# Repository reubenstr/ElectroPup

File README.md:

# ElectroPup

ElectroPup is a DIY 3D-printed quadruped robot using 'low cost' BLDC motors.

[Video of kinematic poses](https://youtu.be/AJn_wCcWlwo)

[Video of walking, turning, strafing](https://youtu.be/YjTVNw8BXlM)

## Basic Specifications

- RPi 5
- 12x BLDC motors
- Auxiliary board w/LCD display
- 9-axis accelerometer/gyro sensor
- 6s Li-Ion battery, ~72wH
- 4.5kg

ElectroPup's control system is coded in Python. For a ROS2 based quadruped, see my previous project [Zuko](https://github.com/reubenstr/zuko).

# Docs

See the docs directory for a setup guide, bill of materials (BOM), 3D printed parts info, and miscellaneous design notes.

# UI

The UI shows the status of the entire system: quadruped joint positions, subsystem status, motor information, inputs, sensors, loop times, etc. The above image shows the simulated quadruped overlapped with real quadruped (based on motor feedback).

The above image shows a virtual circle the feet follow to walk in a circle and the bezier curves used for moving the feet up and down.

The UI is built from the React Native Framework using Expo and runs on web. The app will run on Android without the plot. The entire system runs in dev mode so you can run the simulation and UI from a development PC without physical hardware.

# Kinematics

Inverse kinematics, leg position, and gamepad inputs are verified using the UI.

### Trajectories

Bezier curves, sin arcs, and curvature projection are used to generate trajectories. The plots below are examples of control points configurations. 

The output of `./src/plot/bezier_curve_plot.py`

Rotation is achieved by projecting a linear trajectory onto a curve. The plots are of example projection calculations.

The output of `./src/plot/projection_plot.py`

# Simulation

Simulation is performed in [MuJoCo](https://mujoco.org/) and can be started by running `./src/sim.sh`. Currently, input controlls are only provided by the gamepad. The `ElectroPup.xml` currently does not have approximate masses or inertial so the simulated quadruped is rather bouncy.

# Electronics

## PCBs

PCBs are designed in [KiCad](https://www.kicad.org/) v8 and fabricated by JLCPCB.

### Power Carrier

The Power Carrier PCB provides a main on/off power switch and distributes power to the motor headers. The Power Carrier creates four CAN bus networks one for each leg. Solder jumpers allow merging the front two legs into a single network and the back two legs into another single network.

### Auxiliary Board

The auxiliary board is optional and not required for the quadruped to operate.

Features:
- Powers RPi via terminal header
- LCD display
- Buzzer (variable pitch)
- NeoPixel strips
- RC Servo channel
- I2C expansion
- Button to control LCD and shutdown Raspberry Pi before power off

Provides direct connection to RPi header for the following breakouts:
- IMU (BNO055 via I2C)
- 4x contact inputs or GPIO
- I2S for sound driver (future barks 🐶)
- SBUS to use RC transmitter if BLE gamepad fails in RF congested areas

# Software Architecture

Electropup's software architecture was purposely designed to be simple and to bypass the pain points of using ROS2. See my [Zuko]( https://github.com/reubenstr/zuko) robot quadruped for a ROS2 implementation, abiet outdated. A major downside of this single service architecture is needing to sit and stand the quadruped on every software change vs being able to restart individual services quickly without affecting others (i.e. the motors). However, with the simulated quadruped and UI, most development is not performed on a live quadruped.

# Motors

The motors are MG4010E-i10v3 actuators made by LingKong (LKMTECH) and can be purchased from [Aliexpress](https://www.aliexpress.us/item/3256805950420462.html?spm=a2g0o.order_list.order_list_main.5.32491802no3XMa&gatewayAdapt=glo2usa).

### Specifications
- voltage: 7.4-32V
- communication: CAN 1Mbps
- rated torque: 2.5 N.m
- max torque: 4.5 N.m
- rated current: 3.5 A
- max power: 140 W
- gear ratio: 1:10
- encoders: 18-bit motor, 14-bit reducer
- size: 53mm diameter, 41mm tall
- weight: 238 grams

### MG4010E-i10v3 Pros
- easy to use configuration software over non-proprietary USB to UART hardware
- readable CAN bus communication documentation
- small physical size that works well with the desired frame size of ElectroPup
- non-proprietary power/communications connector (JST-ZH 6-POS)

### MG4010E-i10v3 Cons
- configuration software is Windows only
- closed source firmware
- foreign sourced, complicating the warranty process
- CAN unable to configure all parameters
- UART required to configure error thresholds, motor torque limits (for compliance), etc.
- some motors are more difficult to turn by hand and require slightly more operational current

Future projects will prioritize ODrive compatible drivers.

### Motor Zero Positions

### Motor Tags

### Motor Calibration

The zero-motors.py script is a quick way to verify correct motor configuration and to zero the motors.

# CAN Bus

The CAN bus controller is a [2-Channel Isolated CAN Expansion HAT](https://www.waveshare.com/2-ch-can-hat.htm) from waveshare.

Each CAN controller drives six motors with an average motor update rate of ~70 Hz. This includes fetching encoder position, setting target angle/speed, and getting error states.

# Gamepad

ElectroPup was coded with a PS4 controller in mind, however xBox, PS5, Logitech gamepads may be used with minor software modifications.

# Environment and IDEs 

There are three hardware/software environments described below.

### PC/Laptop - Plotting, Simulation, and Development

Desktop or laptop computer running Ubuntu Desktop (or your preferred flavor of Linux).

Software: VSCode (with remote SSH and PlatformIO extensions), Drawio, LibreOffice, KiCad, OrcaSlicer, Chrome/Firefox

### Raspberry Pi - Quadruped Hardware Driver

The quadruped compute is a Raspberry Pi 5.

The OS is Raspberry Pi OS Lite (Bookworm 64-bit), which is headless, so all development is performed using remote SSH.

### STM32 - Auxiliary Board

An STM32F401 Black Pill dev kit operates the auxiliary board to display the motor and system status on a LCD display and interface with other peripherals such as the buzzer. 

Uses VSCode with PlatformIO on the PC/Laptop for development.

# Parts

The 3D printed parts are printed using Polymaker PolyMax Tough PLA selected for strength and ease of printing. See these excellent blog posts for more information: [cnckitchen](https://www.cnckitchen.com/blog/the-difference-of-pla-and-pla-tested-feat-polymaker) and [edemargerie](https://www.instructables.com/Comparing-Impact-Resistance-of-21-Filaments-for-3D/).

| Color          | Estimated Print Time | Estimated Filament |
| -------------- | -------------------- | ------------------ |
| main (red)     | 25.23 hours          | 742 grams          |
| accent (black) | 3.58 hours           | 92 grams           |

### CAD

Parts are modeled using [OnShape](https://www.onshape.com/en/) which provides free web-based full access for non-commercial use. The links below should have export permissions to allow copying the workspace.

- [Assembly](https://cad.onshape.com/documents/b02341d4ebb7f3e9dd488186)
- [Legs](https://cad.onshape.com/documents/6da583196278caf8e90b3122)
- [Body](https://cad.onshape.com/documents/280c24f1b6bdbe8246159786)
- [Hips](https://cad.onshape.com/documents/428031d0c98bf15dcc9f5c8c)
- [Tools](https://cad.onshape.com/documents/3677b35bffbfedb5a3fd2b26)
- [Parts](https://cad.onshape.com/documents/6d4d4e21394ee725ee8ddb38)
- [PCB](https://cad.onshape.com/documents/c8a855826c37bd92b89d9f0e)
- [Neopixels](https://cad.onshape.com/documents/567292ac55c75b2efa25b7d5)

# Battery Pack 

The battery is a custom 6S1P Li-Ion using 18650s with a load balancing BMS. The 18650's are Sanyo branded and rated at 3250mAH each providing an estimated 72Wh.

The above image is showing work in progress. The [insulation rings](https://imrbatteries.com/products/18650-terminal-insulators-fish-paper-20pcs-green-round-rings) were forgotten during fabrication and really should be mandatory for any battery build. 

The BMS is a HXYP-6S-CW15.

# Future Improvements  

This is a general improvement list for future updates or revisions. 

- add upside down control (the frame supports walking even after flipped)
- apply IMU for smoother gaits
- add center of mass calculations for smoother gaits
- swap battery and RPi positions for better center of mass
- swap foot lag bolt from SAE to metric
- add curvature to lower leg
- add speaker for barks
- add a tail
- add voltage/current sensor (such as an INA228)
- remove STM32 from aux board and use RPI directly for buzzer, LCD, etc.
- create a [MPC](https://en.wikipedia.org/wiki/Model_predictive_control) controller

# Thoughts

- Due to a lower power consumption than estimated, a larger frame and longer legs can be created. A larger frame would support moving the knee motor to the hip area allowing the lower leg to be belt driven. The reduction of mass of the knee will increase center of mass stability and create smoother gaits.
- Future Auxiliary board revisions will remove the STM32 and either drive the LCD directly from the RPi or remove it completely. The extra complexity outweighs the LCD's usefulness, especially when the GUI provides significantly more data.
- Future power carrier PCB revisions will include a voltage/current sensor such as a INA228 and a fuse.
- The carbon rods twist during the run gait which can be reduced by extending the rods through the hip plates and adding face / butt plates. 
- Future revisions will prioritize adding contact sensors that will allow for better terrain handling and future AI training.
- A full architecture refactor splitting major components into services would have the advantages of individual unit testing and keeping the quadruped standing during development.

# Questions

For any questions please post a new [issue](https://github.com/reubenstr/ElectroPup/issues) on the repo's GitHub page.

# Credits

Inverse kinematics and leg points for plotting were sourced from mike4192: [https://github.com/mike4192/](https://github.com/mike4192/).

Using carbon fiber tube as frame supports inspired from [Open Dog 3](https://www.youtube.com/watch?v=ts2l_Em7fpI&list=PLpwJoq86vov8uTgd8_WNgBHFpDYemO-OJ&index=3) by James Bruton.

There are many excellent open source quadruped robot projects at various sizes, costs, and complexity. Below are projects and code examples worth checking out.

- https://github.com/mit-biomimetics/Cheetah-Software
- https://github.com/mike4192/spotMicro
- https://github.com/mike4192/spot_micro_kinematics_python
- https://spotmicroai.readthedocs.io/en/latest/
- https://github.com/adham-elarabawy/open-quadruped
- https://www.youtube.com/jamesbruton
- https://github.com/chvmp/champ
- https://grabcad.com/library/diy-quadruped-robot-1
- https://github.com/Jerome-Graves/yertle
- https://www.youtube.com/@Jorgefer88
- https://www.youtube.com/watch?v=oYnsCE2H6ss
- https://github.com/JackDemeter/quadruped-robot
- https://github.com/reubenstr/zuko

# AI Disclosure

Project concept, aesthetic, engineering design, and original code base were conceived and executed by the author.

Portions of this codebase were reviewed, revised, and written with the assistance of Claude Code (Anthropic).

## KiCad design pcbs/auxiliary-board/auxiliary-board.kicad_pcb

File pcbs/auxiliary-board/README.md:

# TODO / Fixes

- Add version number to silkscreen
- Change terminal footprint to match the now used terminal: WM7877-ND 
- Add a switch for WiFi AP/Client switching
- LCD holes are not aligned and are off slightly
- Change 40 pin header from SMD to through-hold
- Consider adding a second tactile button

# General Thoughts

- Removing the Black Pill in favor of using a STM32 directly on the board will save space and allow the addition of more breakouts such as buttons.

- Removing the LCD PCB and directly connecting a LCD to the board will reduce the height of the board that will decrease the chance of screen damage when the quadruped rolls over.

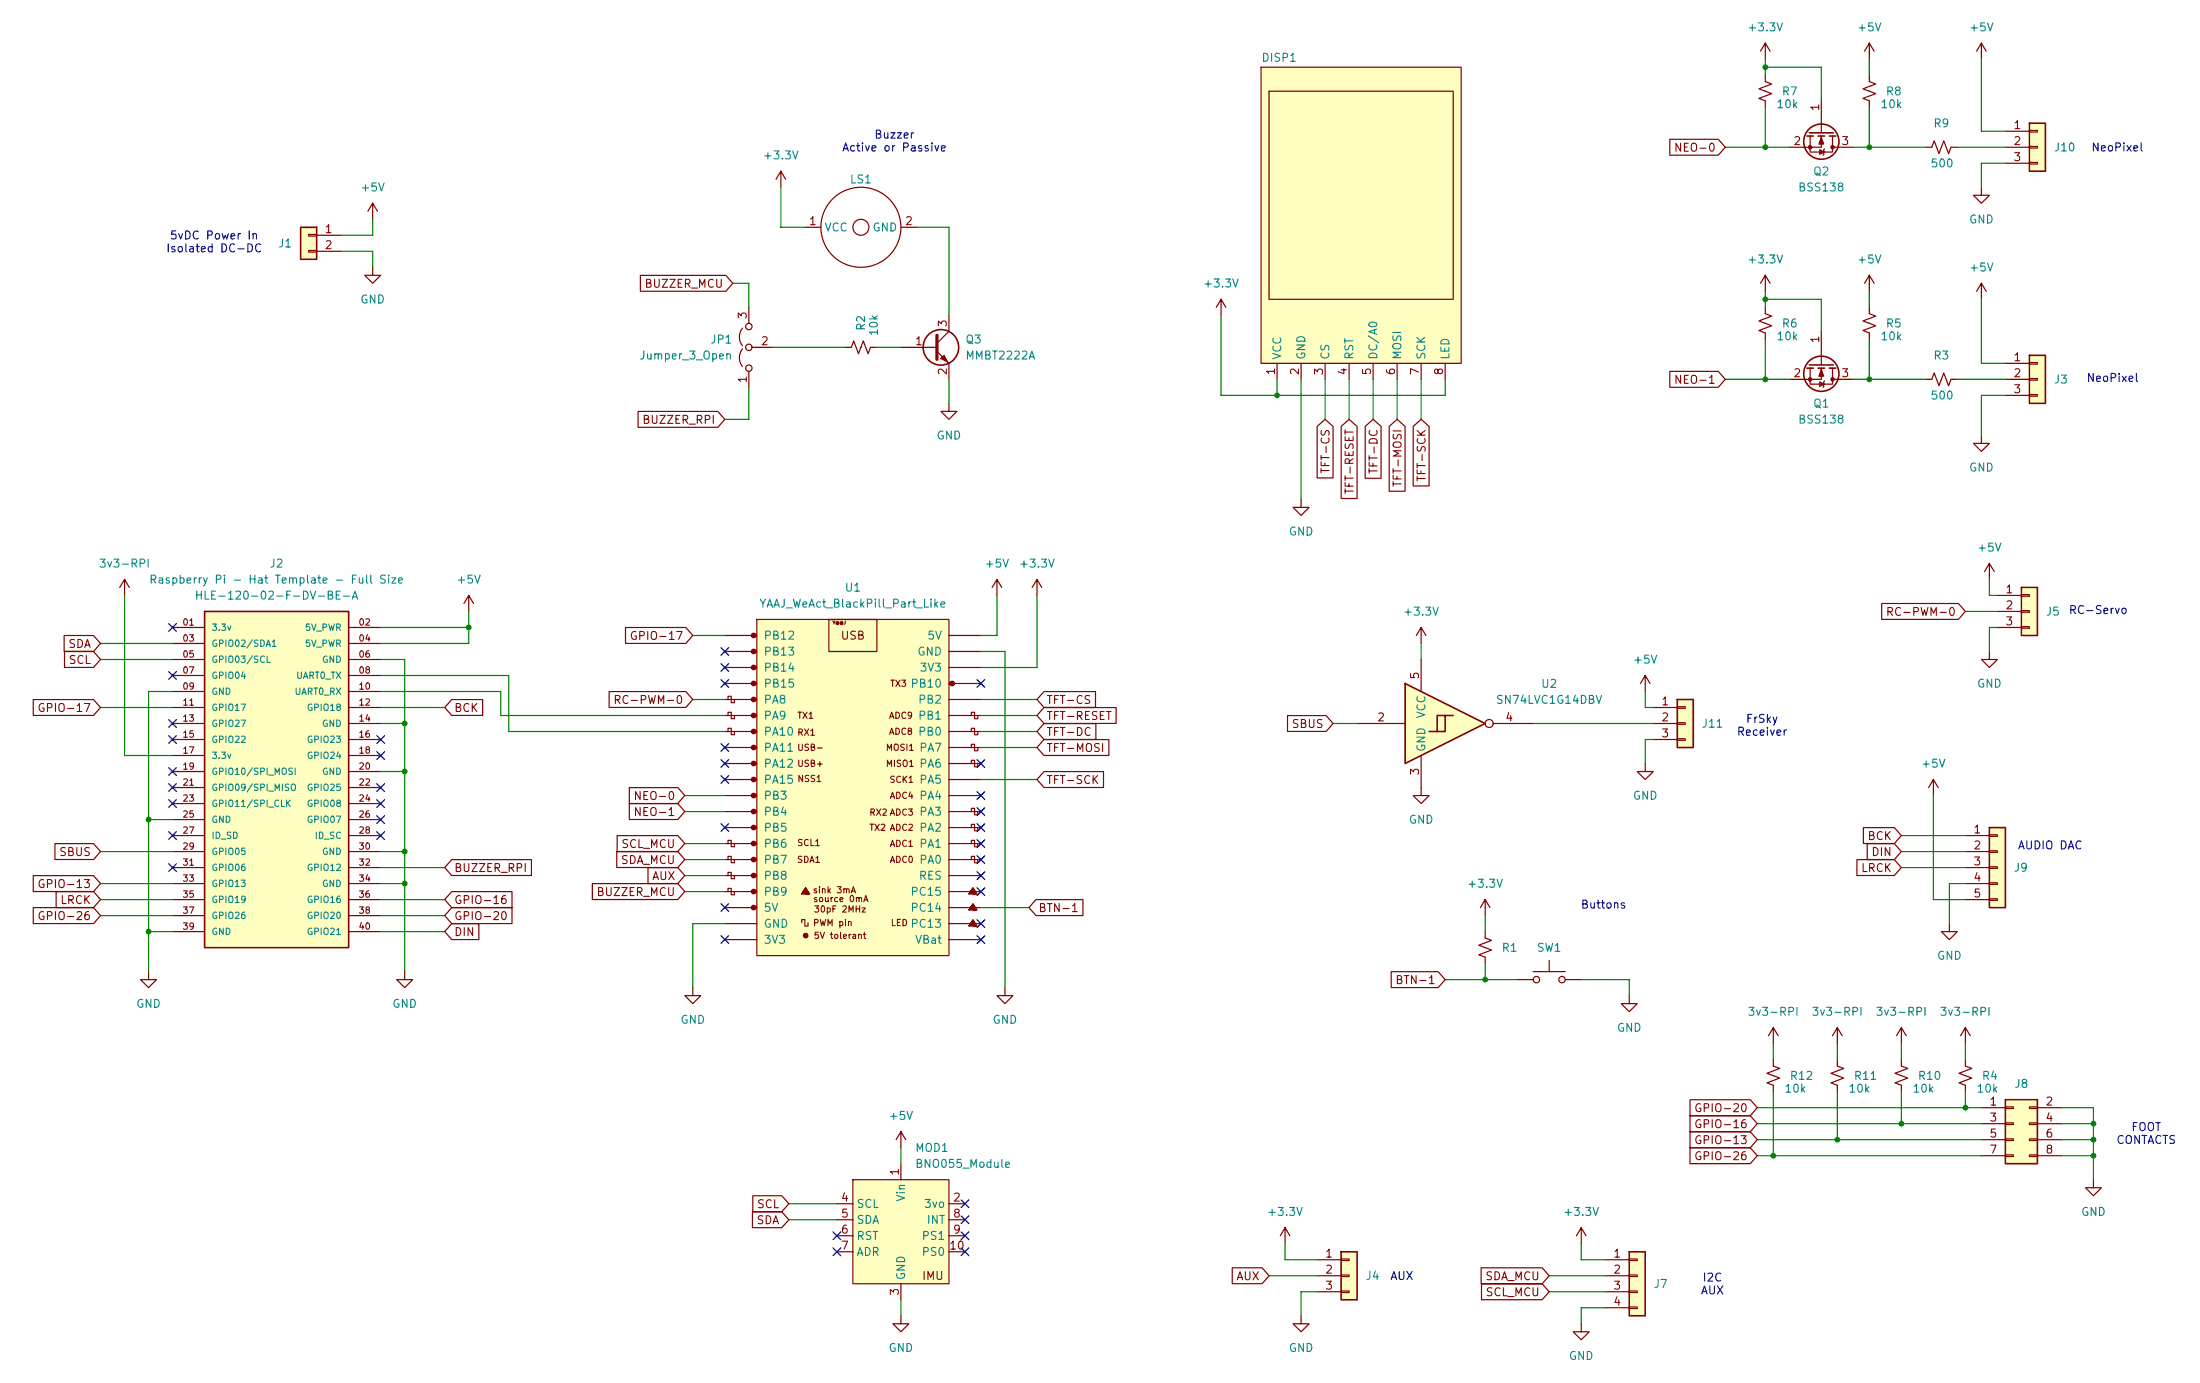
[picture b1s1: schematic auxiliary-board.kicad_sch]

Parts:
DISP1: LCD-Display-1.8-128x160-Hiletgo
J1: Conn_01x02; TerminalBlock_Phoenix_PT-1,5-2-3.5-H_1x02_P3.50mm_Horizontal
J2: Raspberry Pi - Hat Template - Full Size; Raspberry Pi - Hat Template - Full Size Extended
J3, J4, J5, J10, J11: Conn_01x03; JST_ZH_B3B-ZR_1x03_P1.50mm_Vertical
J7: Conn_01x04; JST_ZH_B4B-ZR_1x04_P1.50mm_Vertical
J8: Conn_02x04_Odd_Even; PinHeader_2x04_P2.54mm_Vertical
J9: Conn_01x05; JST_ZH_B5B-ZR_1x05_P1.50mm_Vertical
JP1: Jumper_3_Open; SolderJumper-3_P1.3mm_Open_Pad1.0x1.5mm
LS1: PB-09N23P-03Q_MAL
MOD1: BNO055_Module; BNO055 Module
Q1, Q2: BSS138; SOT-23
Q3: MMBT2222A; SOT-23
R1: R_Small_US; R_1206_3216Metric
R2, R4, R5, R6, R7, R8, R10, R11, R12: 10k; R_1206_3216Metric
R3, R9: 500; R_1206_3216Metric
SW1: SW_Push; SW_PUSH_6mm_H4.3mm
U1: YAAJ_WeAct_BlackPill_Part_Like; Blackpill WeAct
U2: SN74LVC1G14DBV; SOT-23-5

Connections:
3v3-RPI: J2.17 (3.3v), R4.2, R10.2, R11.2, R12.2
+3.3V: DISP1.1 (VCC), DISP1.8 (LED), J4.1, J7.1, LS1.1 (VCC), Q1.1 (G), Q2.1 (G), R1.2, R6.2, R7.2, U1.38 (3V3), U2.5 (VCC)
+5V: J1.1, J2.02 (5V_PWR), J2.04 (5V_PWR), J3.1, J5.1, J9.5, J10.1, J11.1, MOD1.1 (Vin), R5.2, R8.2, U1.40 (5V)
AUX: J4.2, U1.16 (PB8)
BCK: J2.12 (GPIO18), J9.1
BTN-1: R1.1, SW1.1, U1.23 (PC14)
BUZZER_MCU: JP1.3 (B), U1.17 (PB9)
BUZZER_RPI: J2.32 (GPIO12), JP1.1 (A)
DIN: J2.40 (GPIO21), J9.2
GND: DISP1.2 (GND), J1.2, J2.06 (GND), J2.09 (GND), J2.14 (GND), J2.20 (GND), J2.25 (GND), J2.30 (GND), J2.34 (GND), J2.39 (GND), J3.3, J4.3, J5.3, J7.4, J8.2, J8.4, J8.6, J8.8, J9.4, J10.3, J11.3, MOD1.3 (GND), Q3.2 (E), SW1.2, U1.19 (GND), U1.39 (GND), U2.3 (GND)
GPIO-13: J2.33 (GPIO13), J8.5, R11.1
GPIO-16: J2.36 (GPIO16), J8.3, R10.1
GPIO-17: J2.11 (GPIO17), U1.1 (PB12)
GPIO-20: J2.38 (GPIO20), J8.1, R4.1
GPIO-26: J2.37 (GPIO26), J8.7, R12.1
LRCK: J2.35 (GPIO19), J9.3
NEO-0: Q2.2 (S), R7.1, U1.11 (PB3)
NEO-1: Q1.2 (S), R6.1, U1.12 (PB4)
unnamed: J2.10 (UART0_RX), U1.6 (PA9)
unnamed: J2.08 (UART0_TX), U1.7 (PA10)
unnamed: J3.2, R3.2
unnamed: J10.2, R9.2
unnamed: J11.2, U2.4
unnamed: JP1.2 (C), R2.2
unnamed: LS1.2 (GND), Q3.3 (C)
unnamed: Q1.3 (D), R3.1, R5.1
unnamed: Q2.3 (D), R8.1, R9.1
unnamed: Q3.1 (B), R2.1
RC-PWM-0: J5.2, U1.5 (PA8)
SBUS: J2.29 (GPIO05), U2.2
SCL: J2.05 (GPIO03/SCL), MOD1.4 (SCL)
SCL_MCU: J7.3, U1.14 (PB6)
SDA: J2.03 (GPIO02/SDA1), MOD1.5 (SDA)
SDA_MCU: J7.2, U1.15 (PB7)
TFT-CS: DISP1.3 (CS), U1.36 (PB2)
TFT-DC: DISP1.5 (DC/A0), U1.34 (PB0)
TFT-MOSI: DISP1.6 (MOSI), U1.33 (PA7)
TFT-RESET: DISP1.4 (RST), U1.35 (PB1)
TFT-SCK: DISP1.7 (SCK), U1.31 (PA5)

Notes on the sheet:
Buzzer Active or Passive
AUDIO DAC
AUX
Buttons
FrSky Receiver
FOOT CONTACTS
NeoPixel
I2C AUX
RC-Servo
5vDC Power In Isolated DC-DC

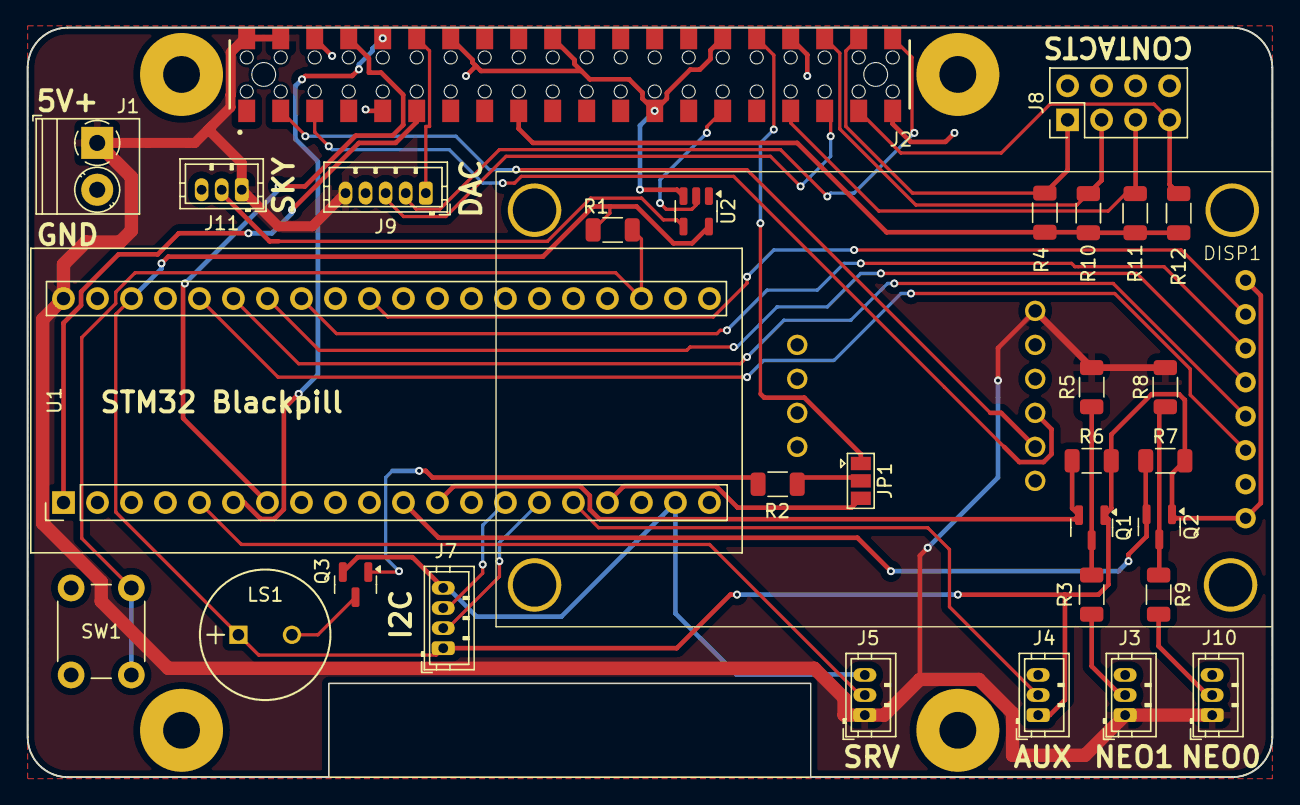
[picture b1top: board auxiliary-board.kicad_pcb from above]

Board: 2 copper layers, 93.0 x 56.0 mm, 32 parts (1 on the bottom side), 39 nets.

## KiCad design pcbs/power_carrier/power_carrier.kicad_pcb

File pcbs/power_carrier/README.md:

# TODO / Fixes

- Add voltage/current sensor such as a INA228
- Add revision number to silkscreen
- Optional: Add motor tags (ex, FLA, FLH, FLK) to silkscreen
- Move 5vDC terminal away from RPi as this blocks the power switch if a RPi 5 is used.
- Some of the PCB may be removed to save weight, perhaps under the battery.

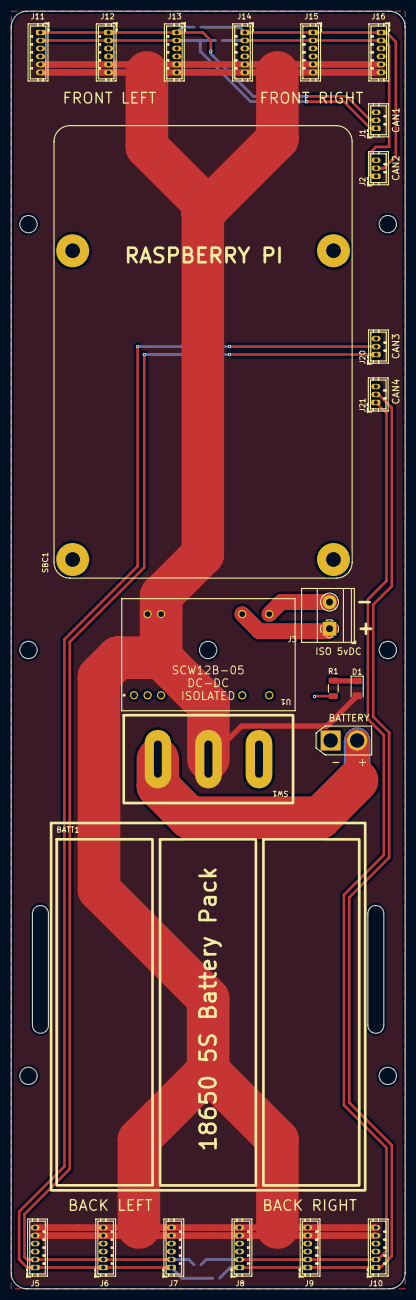
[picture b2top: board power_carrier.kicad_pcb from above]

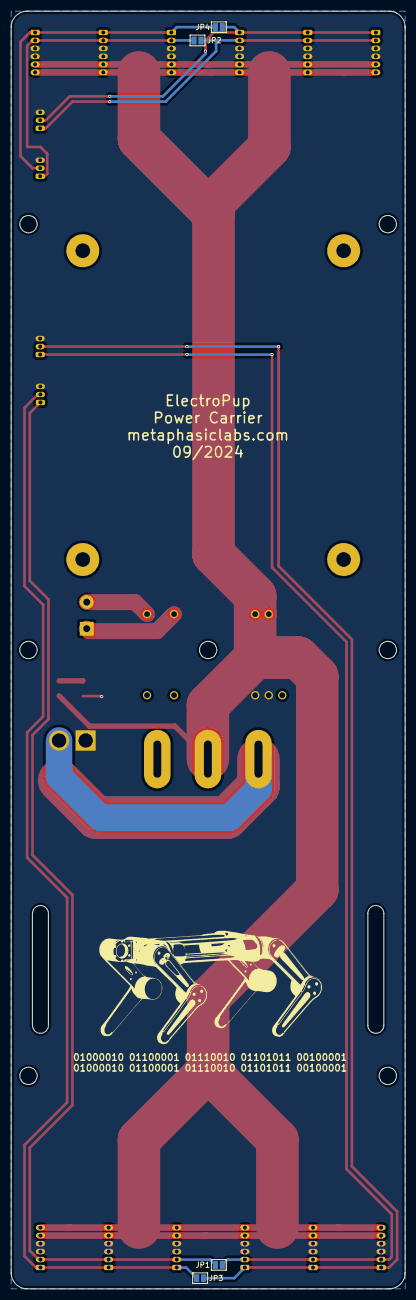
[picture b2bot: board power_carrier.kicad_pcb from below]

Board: 2 copper layers, 74.0 x 240.0 mm, 28 parts (4 on the bottom side), 14 nets.

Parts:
BATT1: 18650 6S Battery Pack - Footprint Only
D1: LED; LED_1206_3216Metric
J1, J2, J20, J21: Conn_01x03; JST_ZH_B3B-ZR_1x03_P1.50mm_Vertical
J3: Conn_01x02; TerminalBlock_Phoenix_MKDS-1,5-2_1x02_P5.00mm_Horizontal
J4: AMASS Connector; AMASS_XT30U-M_1x02_P5.0mm_Vertical
J5, J6, J7, J8, J9, J10, J11, J12, J13, J14, J15, J16: Conn_01x06; JST_ZH_B6B-ZR_1x06_P1.50mm_Vertical
JP1, JP2, JP3, JP4: SolderJumper_2_Open; SolderJumper-2_P1.3mm_Open_Pad1.0x1.5mm
R1: R_Small_US; R_1206_3216Metric
SBC1: RASPBERRY_PI_4B - Footprint Only
SW1: SW_SPST; CRE22F4DBBNE
U1: SCW12B-05; SCW12B-05_MWU

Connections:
+BATT: D1.2 (A), J5.5, J5.6, J6.5, J6.6, J7.5, J7.6, J8.5, J8.6, J9.5, J9.6, J10.5, J10.6, J11.5, J11.6, J12.5, J12.6, J13.5, J13.6, J14.5, J14.6, J15.5, J15.6, J16.5, J16.6, SW1.2 (B), U1.22 (+VIN), U1.23 (+VIN)
/CAN1 HIGH: J1.1, J11.2, J12.2, J13.2, JP2.1 (A)
/CAN1 LOW: J1.2, J11.1, J12.1, J13.1, JP4.1 (A)
/CAN2 HIGH: J2.1, J14.2, J15.2, J16.2, JP2.2 (B)
/CAN2 LOW: J2.2, J14.1, J15.1, J16.1, JP4.2 (B)
/CAN3 HIGH: J5.2, J6.2, J7.2, J20.1, JP1.1 (A)
/CAN3 LOW: J5.1, J6.1, J7.1, J20.2, JP3.1 (A)
/CAN4 HIGH: J8.2, J9.2, J10.2, J21.1, JP1.2 (B)
/CAN4 LOW: J8.1, J9.1, J10.1, J21.2, JP3.2 (B)
/ISO 5vDC GND: J3.2, U1.14 (+VOUT)
/ISO 5vDC+: J3.1, U1.16 (-VOUT)
GND: J1.3, J2.3, J4.1 (-), J5.3, J5.4, J6.3, J6.4, J7.3, J7.4, J8.3, J8.4, J9.3, J9.4, J10.3, J10.4, J11.3, J11.4, J12.3, J12.4, J13.3, J13.4, J14.3, J14.4, J15.3, J15.4, J16.3, J16.4, J20.3, J21.3, R1.2, U1.2 (-VIN), U1.3 (-VIN)
unnamed: D1.1 (K), R1.1
unnamed: J4.2 (+), SW1.1 (A)

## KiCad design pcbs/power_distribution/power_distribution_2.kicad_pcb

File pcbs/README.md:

# PCBs

PCBs are designed in [KiCad](https://www.kicad.org/) (v8)

Custom libraries used for these projects may be found on my github repo: [https://github.com/reubenstr/kicad-libraries](https://github.com/reubenstr/kicad-libraries)

See the README.md in each project for next revision error fixes.

## Auxiliary Board

This board uses a STM32 co-processor to add the following functionality to the system:

- LCD display for error indication and status such as battery levels
- 1x buzzer
- 2x Neopixel strips
- 1x RC servo
- 1x button

This board also provides the following Raspberry Pi connection breakouts:
- BNO055 IMU
- SBUS FrSKY RC receiver input
- I2S header
- 4x contact switches (or aux GPIO)

## Power Carrier

This board provides the following functionality:
- Power distribution for the actuators
- CAN bus networks for the actuators
- Isolated DC-DC for the Raspberry Pi
- Main power On/Off switch
- Battery holder and power connection

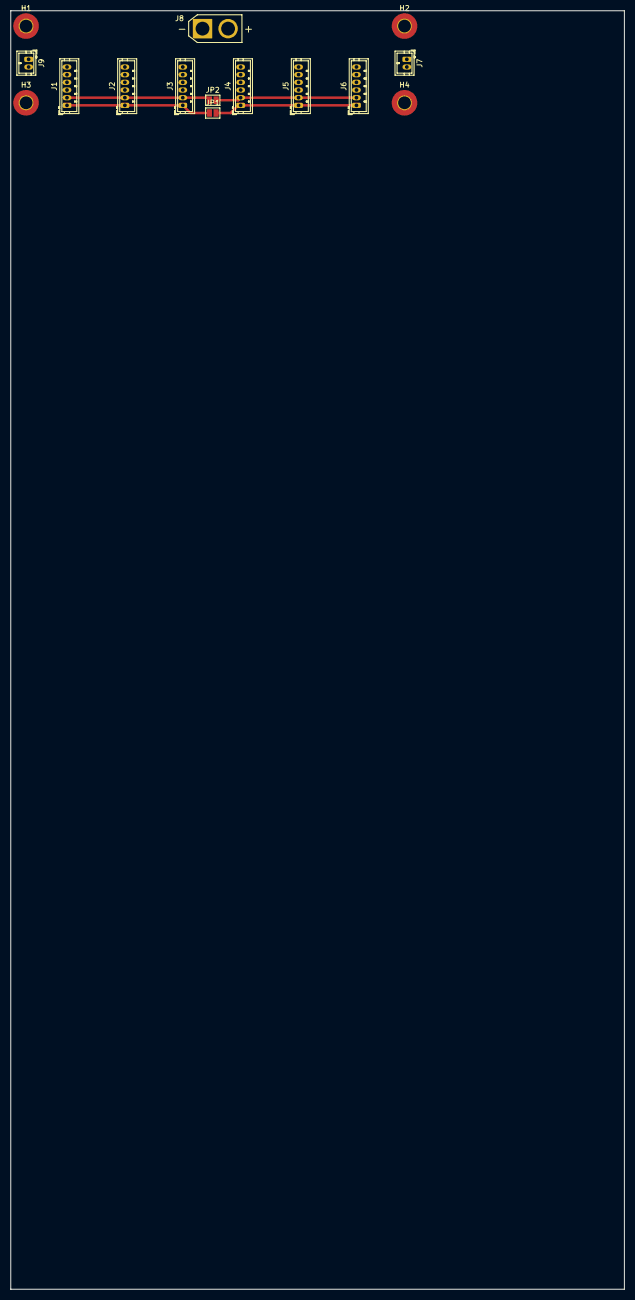
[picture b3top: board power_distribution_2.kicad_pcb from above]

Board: 2 copper layers, 120.0 x 250.0 mm, 15 parts (0 on the bottom side), 5 nets.

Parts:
H1, H2, H3, H4: MountingHole; MountingHole_2.5mm_Pad_TopBottom
J1, J2, J3, J4, J5, J6: Conn_01x06; JST_ZH_B6B-ZR_1x06_P1.50mm_Vertical
J7, J9: Conn_01x02; JST_ZH_B2B-ZR_1x02_P1.50mm_Vertical
J8: Conn_01x02; AMASS_XT30U-M_1x02_P5.0mm_Vertical
JP1, JP2: SolderJumper_2_Open; SolderJumper-2_P1.3mm_Open_Pad1.0x1.5mm

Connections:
+BATT: J1.5, J1.6, J2.5, J2.6, J3.5, J3.6, J4.5, J4.6, J5.5, J5.6, J6.5, J6.6, J8.2
/CAN1 HIGH: J1.2, J2.2, J3.2, J9.1, JP2.1 (A)
/CAN2 HIGH: J4.2, J5.2, J6.2, J7.1, JP2.2 (B)
/CAN2 LOW: J1.1, J2.1, J3.1, J4.1, J5.1, J6.1, J7.2, J9.2, JP1.1 (A), JP1.2 (B)
GND: J1.3, J1.4, J2.3, J2.4, J3.3, J3.4, J4.3, J4.4, J5.3, J5.4, J6.3, J6.4, J8.1

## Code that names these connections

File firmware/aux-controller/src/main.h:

///////////////////////////////////////////////////////////////////////////////
// Pins
///////////////////////////////////////////////////////////////////////////////

#define PIN_BTN_1 PC14
#define PIN_RPI_HEARTBEAT PB12
#define PIN_MCU_BUZZER PB9
#define PIN_NEO_0 PB3
#define PIN_NEO_1 PB4

///////////////////////////////////////////////////////////////////////////////
// Timings
///////////////////////////////////////////////////////////////////////////////

const uint32_t heartbeatBlinkRateMs{250};
const uint32_t noCommsTimeoutMs{1000};
const uint32_t rpiHeartbeatTimeoutMs{250};
const uint32_t byteLongPressActivationMs{3000};

///////////////////////////////////////////////////////////////////////////////
// General
///////////////////////////////////////////////////////////////////////////////

const float gamepadLowBatteryPercentThreashold{0.25};
const float systemLowBatteryPercentThreashold{0.25};

///////////////////////////////////////////////////////////////////////////////
// Display
///////////////////////////////////////////////////////////////////////////////

enum class Page
{
    SPLASH,
    SYSTEM,
    BATTERY
};

const int numSystemStatus{12};
const char *systemStatusStrings[numSystemStatus] = {"RPI", "SFT", "JOY", "LIM", "JA", "IK", "CAN", "OTe", "UVo", "MCo", "IMU", "---"};
const char *motorStatusStrings[] = {"FLA", "FLH", "FLK", "FRA", "FRH", "FRK", "BLA", "BLH", "BLK", "BRA", "BRH", "BRK"};

///////////////////////////////////////////////////////////////////////////////
// Message and Data Structs
///////////////////////////////////////////////////////////////////////////////

bool systemErrors[numSystemStatus];

const int numMotors{12};
bool motorOns[numMotors];
bool motorErrors[numMotors];

struct SystemValues
{
    float batteryVoltage{0};
    float joystickBatteryPercentage{0};
} systemValues;


#pragma pack(1)
struct StatusData
{
    bool joystickError;

    bool physicalLimitError;
    bool jointAngleError;
    bool inverseKinematicsError;

    bool canError;
    bool overTemperatureError;
    bool underVoltageError;
    bool motorCommunicationError;

    bool imuError;

    bool motorOns[numMotors];
    bool motorErrors[numMotors];

    float batteryVoltage;
    float joystickBatteryPercentage;
};

enum class MessageType : uint8_t
{
    STATUS = 0,
    PLAY_SOUND,
    SHUTDOWN_RPI
};

#pragma pack(1)
struct StatusMessage
{
    MessageType messageType;
    StatusData statusData;
    uint32_t crc32;
};

#pragma pack(1)
struct PlaySoundMessage
{
    MessageType messageType;
    uint8_t sequenceId;
    uint32_t crc32;
};

#pragma pack(1)
struct ShutDownMessage
{
    MessageType messageType;
    uint32_t crc32;

    ShutDownMessage()
    {
        messageType = MessageType::SHUTDOWN_RPI;
    }
};

///////////////////////////////////////////////////////////////////////////////
// Prototypes
///////////////////////////////////////////////////////////////////////////////

void InitDisplay();
void UpdateDisplay(bool forceRefresh);
void DisplaySplashPage();
void DisplaySystemPage(bool forceRefresh);
void DisplayBatteryPage(bool forceRefresh);

bool IsLowBattery();
bool IsError();

///////////////////////////////////////////////////////////////////////////////
// Helpers
///////////////////////////////////////////////////////////////////////////////

// TODO: an assert of other warning should be applied of the string is not found.

int getIndexFromStatusString(const char *status)
{
    for (int i = 0; i < numSystemStatus; ++i)
    {
        if (strcmp(status, systemStatusStrings[i]) == 0)
        {
            return i;
        }
    }
    return -1;
}

int getValueFromStatusString(const char *status)
{
    int index = getIndexFromStatusString(status);

    if (index != -1)
        return systemErrors[index];
    else
        return false;
}

void setValueFromStatusString(const char *status, bool state)
{
    int index = getIndexFromStatusString(status);

    if (index != -1)
        systemErrors[index] = state;
}

///////////////////////////////////////////////////////////////////////////////
// CRC
///////////////////////////////////////////////////////////////////////////////

uint32_t crc32(uint8_t *data, int length)
{
    const uint32_t POLYNOMIAL = 0x04C11DB7;
    uint32_t crc = 0xFFFFFFFF;

    for (size_t i = 0; i < length; i++)
    {
        crc ^= data[i] << 24;
        for (int j = 0; j < 8; ++j)
        {
            if (crc & 0x80000000)
            {
                crc = (crc << 1) ^ POLYNOMIAL;
            }
            else
            {
                crc <<= 1;
            }
            crc &= 0xFFFFFFFF;
        }
    }
    return crc ^ 0xFFFFFFFF;
}

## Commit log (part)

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2024-08-25 first
2024-09-02 CAN motor controller tests implemented
2024-09-02 add CAN test scripts
2024-09-05 PCB update
2024-09-07 PCB update.
2024-09-11 PCB update; project name change
2024-09-21 sim model update
2024-09-21 bringing in previous quadruped robot control scripts; updated gamepad
2024-09-22 minor updates, cleanup
2024-09-22 joint angle config updates and model updates
2024-09-22 IK tweak
2024-09-24 added kinematics plot repo
2024-09-24 added translation input to stickfigure repo
2024-09-24 kinematics plot update
2024-09-24 classed motion parameters, added motion parameters to gamepadinteface
2024-09-25 new kinematics flowing to sim
2024-09-25 added custom exceptions to handle joints out of bounds in IK
2024-09-26 added joint angle check and domain check to IK
2024-09-26 clean up and added comments
2024-09-26 plot.py cleanup, prep for pub
2024-09-27 sim.py working again after updating quadruped code; fixed imports
2024-09-27 model xml update to understand error of contacts
2024-09-27 changed model xml angles to match kinematics angles (zero positions)
2024-09-27 gamepad disconnect logic updated to provide disconnect check to main thread
2024-09-29 started aux display code
2024-09-29 aux pcb update
2024-09-30 aux display update
2024-10-06 motor source upload; file reorg
2024-10-06 debugging after moved to RPi
2024-10-07 debugging
2024-10-09 motor calibration script update
2024-10-09 zero motor script update
2024-10-10 updated can interface with better error detection
2024-10-13 notes update
2024-10-17 classed live; added control events to JS; fixed motor on/off all bug
2024-10-17 add controller events, removed uneeded callbacks
2024-10-17 added to kinetic state machine
2024-10-18 motor loop now always checks angles and status, reduces timing bugs
2024-10-18 get multi angle fix; added limits and limit check to error states
2024-10-18 added startup offset to motors to compensate for 0-360 val
2024-10-19 update motor zero utility with offset flags
2024-10-19 update plot with gamepad updates
2024-10-19 plot.py update to handle no gamepad connected
2024-10-19 gen backup
2024-10-20 power carrier PCB fix
2024-10-24 source rename to src
2024-10-24 joystick interface rework from polling to event based
2024-10-24 gamepad.py update to include non-blocking connects, reconnects, no exception error handling, etc.
2024-10-25 python source and package reor
2024-10-25 sim update with new gamepad; body/leg dict fixes
2024-10-25 live.py updated with gamepad changes
2024-10-25 cad parts cleanup; parts readme added with links to onshape docs
2024-10-25 doc update and cleanup
2024-10-25 motor labels added, wireframe gif added
2024-10-26 aux firmware update: added errors to message and other timeout handlers
2024-10-26 aux firmware color logic update; added heartbeat check
2024-10-26 aux update; added heartbeak, messaging, and more
2024-10-27 PCB notes update
2024-10-27 added buzzer and sequences to aux MCU
2024-10-27 added play sound command to aux firmware
2024-10-27 added play sounds to aux
2024-10-27 aux board scripts update; includes shutdown command
2024-10-27 pcb readme added, pcb nodes updated
2024-10-27 live.py update: fixes, loop sleep controller, etc.
2024-10-27 added PID setter to motor interface; add default PID to motors
2024-10-28 aux.py fixes, added aux to live.py, misc fixes
2024-10-28 aux firmware status message fixes
2024-10-28 live.py loop cleanup and abstraction
2024-10-29 moved motors.py from thread base to simple thread implementation to allow thread restarts
2024-10-29 live.py error reporting bug fixes
2024-10-29 added more status errors, LCS rearrange, error string protection added
2024-10-29 status bug fix
2024-10-29 start IMU code
2024-10-30 added lie down command and pose
2024-10-30 lie down action bug fix
2024-10-31 added neopixel strip class and a few starting patterns
2024-10-31 added random colors to neopixel class
2024-11-02 added live.py service, added reset arugment to live.py
2024-11-02 gamepad battery percent fix and update
2024-11-02 kinematics bug fix!
2024-11-02 misc. plot changes
2024-11-02 bug fix: pose no longer reverts to last pose after lie down
2024-11-02 push assets
2024-11-02 sim fix, asset upload, doc update
2024-11-02 doc update
2024-11-02 readme.md update
2024-11-03 minor bug fix with low aux rate
2024-11-03 aux rate bug fix, bool reorg minor
2024-11-03 docs update
2024-11-04 neopixel bug fix
2024-11-04 aux board joy status color bug fix
2025-07-26 refactor started
2025-07-27 cleanup
2025-07-27 updated error checking
2025-07-27 starting UI and forwarder add
2025-07-27 three.js plot showing quad
2025-07-27 adding gamepad... need to update height_trans convention
2025-07-27 gamepad inputs fixed into quad
2025-07-27 rotate model
2025-07-28 bias_walk trajectory displayed and properly rotated
2025-07-28 gaits started
2025-07-28 quad/leg flow rework
2025-07-28 ik_params flowing, feet walking
2025-07-28 gait and gait_planner cleanup
2025-07-28 bending traj for rotation
2025-07-28 clean up
2025-07-28 add motion loop time
2025-07-29 misc cleanup, touches
2025-07-29 added hardware.py
2025-07-29 gait gait planner refactor
2025-07-29 state machines cleanups
2025-07-29 update state machine, removed system
2025-07-29 transitions started
2025-07-30 transitions working
2025-07-30 transition and other cleanup
2025-07-30 applied transitions to gait changes
2025-07-30 adding motor state to UI, etc/
2025-07-30 updated aux
2025-07-30 motor live test working
2025-07-30 param cleanup
2025-07-30 added live quadruped and passing angles
2025-07-30 protected standby into stand motionState
2025-07-31 update gamepad with better soc
2025-07-31 idle transition created, transition applied to sit, etc.
2025-07-31 starting refactor to use angular velocity
2025-07-31 soft t started
2025-07-31 t cleanup
2025-07-31 input v f bugfix
2025-08-01 created hard transition between abrupt angle changes
2025-08-01 moved ik and ja errors into quad
2025-08-01 zero script updated
2025-08-01 add requirements
2025-08-01 RPI setup
2025-08-02 heartbeat working, docs updated, scripts updated
2025-08-02 add ground penetration check and prevention
2025-08-02 working on setting up live motors, status report bug fix
2025-08-02 can lock fixes
2025-08-02 reconnect aux shutdown command on btn press
2025-08-03 zero script fixes, doc updates, misc
2025-08-03 update mojocu simulation
2025-08-03 motion added to mujoco simulation
2025-08-03 .gitignore update
2025-08-03 ui update
2025-08-03 added x comp, under test
2025-08-03 trajectory_planner optimization
2025-08-03 transition optimization
2025-08-04 testing, minor bug fixes
2025-08-09 motors into motion for faster data handling
2025-08-09 clean up, renames, etc.
2025-08-09 ui updates
2025-08-09 motion parms update with props and cleanups
2025-08-09 added server as a service and install script
2025-08-09 cor calc rework
2025-08-10 stash
2025-08-10 lateral working, quadrant corrections applied
2025-08-10 imu connect, passing data
2025-08-10 cor cleanup
2025-08-10 stride scale added
2025-08-10 run added
2025-08-10 imu data applied to sim quad
2025-08-10 ui timeout bug fix
2025-08-10 minor cleanup
2025-08-11 plot cleanup and additions
2025-08-17 add play sounds, add low batt check, change neo colors
2025-08-17 add climb gait
2025-08-17 input / motion param format updatE
2025-08-17 main arg updates and misc
2025-08-17 add main install script
2025-08-17 doc update, ui build
2025-08-17 flask path error
2025-08-17 web ui build
2025-08-17 icons
2025-08-17 flask route fix
2025-08-31 added wifi hotspot and reconnect, under test
2025-08-31 wifi update
2025-08-31 wifi fix
2025-11-15 update wifi, misc.
2025-11-15 moved service helpers into class
2025-11-15 remove command callback replaced with queue
2025-11-15 bugfixes
2025-11-15 apply sim yaw to live yaw
